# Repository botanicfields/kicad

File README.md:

# kicad
Projects

BF-002: Terminator for TLC5940

BF-005: 16-Segment LED controlled by TLC5940

BF-010: M5Stack interface for TLC5940 and HT16K33

BF-012: Arduino-Uno interface for TLC5940

libraries and footprints used by the projects above, or not used.

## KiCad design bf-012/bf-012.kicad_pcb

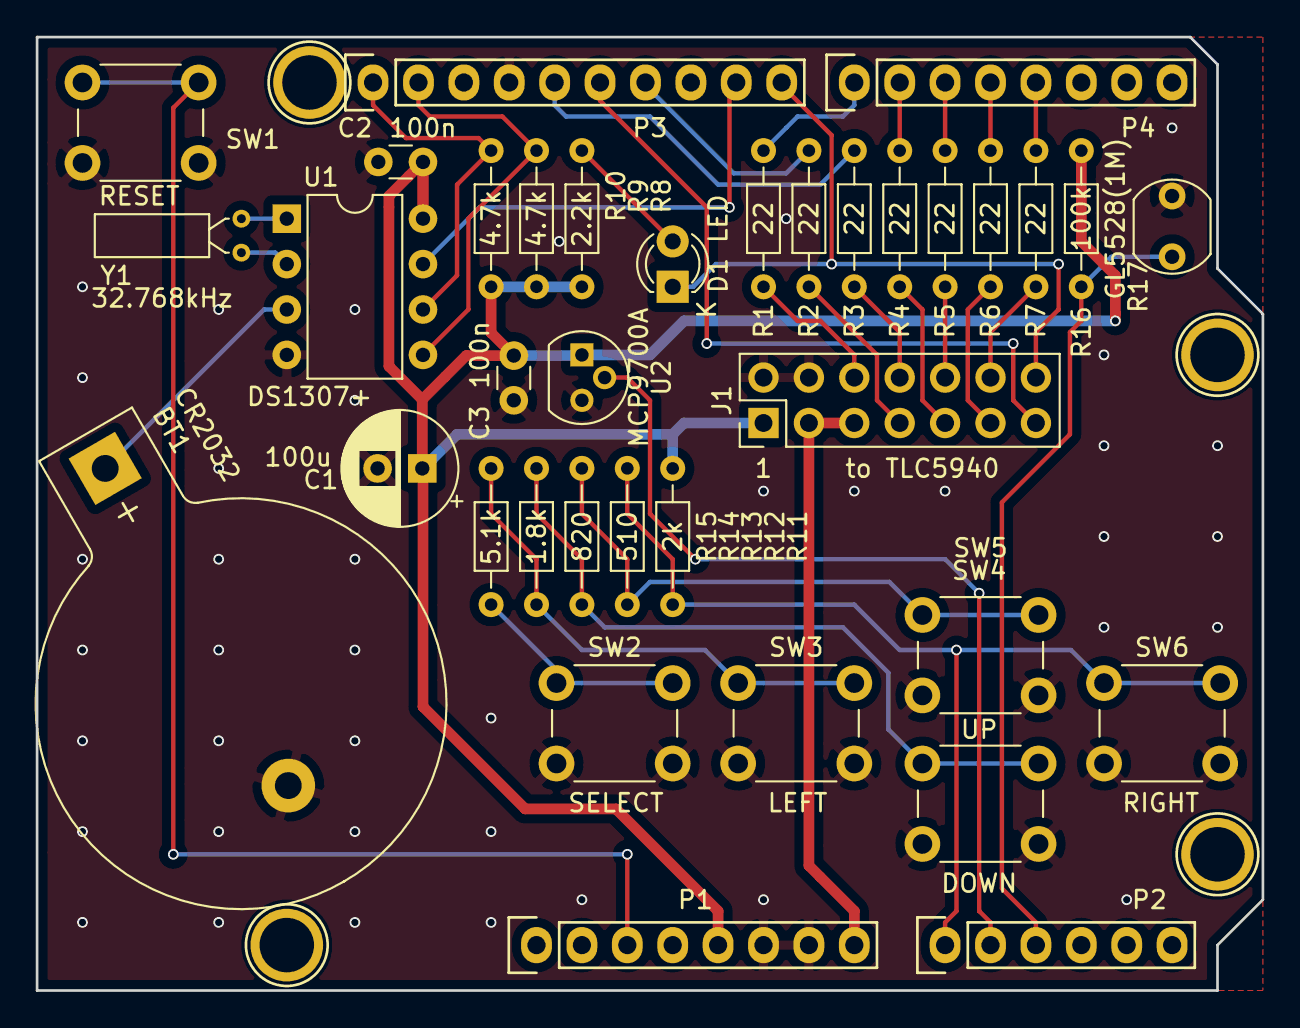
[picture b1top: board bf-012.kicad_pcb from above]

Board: 2 copper layers, 68.6 x 53.3 mm, 40 parts (0 on the bottom side), 34 nets.

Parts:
BT1: CR2032; BF@BatteryHolder_Keystone_103_1x20mm
C1: 100u; CP_Radial_D6.3mm_P2.50mm
C2, C3: 100n; C_Disc_D3.0mm_W1.6mm_P2.50mm
D1: LED; LED_D3.0mm
J1: Conn_02x07_Odd_Even; PinHeader_2x07_P2.54mm_Vertical
P1: Power; Socket_Strip_Arduino_1x08
P2: Analog; Socket_Strip_Arduino_1x06
P3: Digital; Socket_Strip_Arduino_1x10
P4: Digital; Socket_Strip_Arduino_1x08
P5, P6, P7, P8: CONN_01X01; Arduino_1pin
R1, R2, R3, R4, R5, R6, R7: 22; R_Axial_DIN0204_L3.6mm_D1.6mm_P7.62mm_Horizontal
R8: 2.2k; R_Axial_DIN0204_L3.6mm_D1.6mm_P7.62mm_Horizontal
R9, R10: 4.7k; R_Axial_DIN0204_L3.6mm_D1.6mm_P7.62mm_Horizontal
R11: 2k; R_Axial_DIN0204_L3.6mm_D1.6mm_P7.62mm_Horizontal
R12: 510; R_Axial_DIN0204_L3.6mm_D1.6mm_P7.62mm_Horizontal
R13: 820; R_Axial_DIN0204_L3.6mm_D1.6mm_P7.62mm_Horizontal
R14: 1.8k; R_Axial_DIN0204_L3.6mm_D1.6mm_P7.62mm_Horizontal
R15: 5.1k; R_Axial_DIN0204_L3.6mm_D1.6mm_P7.62mm_Horizontal
R16: 100k; R_Axial_DIN0204_L3.6mm_D1.6mm_P7.62mm_Horizontal
R17: GL5528(1M); R_LDR_5.1x4.3mm_P3.4mm_Vertical
SW1: RESET; SW_PUSH_6mm
SW2: SELECT; SW_PUSH_6mm
SW3: LEFT; SW_PUSH_6mm
SW4: DOWN; SW_PUSH_6mm
SW5: UP; SW_PUSH_6mm
SW6: RIGHT; SW_PUSH_6mm
U1: DS1307+; DIP-8_W7.62mm
U2: MCP9700A; TO-92
Y1: 32.768kHz; Crystal_DS26_D2.0mm_L6.0mm_Horizontal

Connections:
+5V: C1.1, C2.1, C3.1, J1.1, P1.5, R8.1, R9.1, R10.1, R11.1, R16.1, U1.8, U2.1
/3(**): P4.5, R7.1
/4: P4.4, R6.1
/5(**): P4.3, R5.1
/6(**): P4.2, R4.1
/7: P4.1, R1.1
/8: D1.1, J1.14, P3.10
/9(**): P3.9, U1.7
/11(**MOSI): P3.7, R2.1
/12(MISO): J1.13, P3.6
/13(SCK): P3.5, R3.1
/A0: P2.1, R11.2, R12.1, SW6.1
/A1: P2.2, U2.2
/A2: P2.3, R16.2, R17.1
/A4(SDA): P3.2, R9.2, U1.5
/A5(SCL): P3.1, R10.2, U1.6
/BLANK: J1.10, R5.2
/DCPRG: J1.11, R6.2
/GSCLK: J1.12, R7.2
/Reset: P1.3, SW1.1
/SCLK: J1.8, R3.2
/SIN: J1.7, R2.2
/VPRG: J1.6, R1.2
/Vin: J1.3, J1.5, P1.8
/XLAT: J1.9, R4.2
GND: BT1.2, C1.2, C2.2, C3.2, J1.2, J1.4, P1.6, P1.7, P3.4, R17.2, SW1.2, SW2.2, SW3.2, SW4.2, SW5.2, SW6.2, U1.4, U2.3
unnamed: BT1.1, U1.3
unnamed: D1.2, R8.2
unnamed: R12.2, R13.1, SW5.1
unnamed: R13.2, R14.1, SW4.1
unnamed: R14.2, R15.1, SW3.1
unnamed: R15.2, SW2.1
unnamed: U1.1, Y1.1
unnamed: U1.2, Y1.2

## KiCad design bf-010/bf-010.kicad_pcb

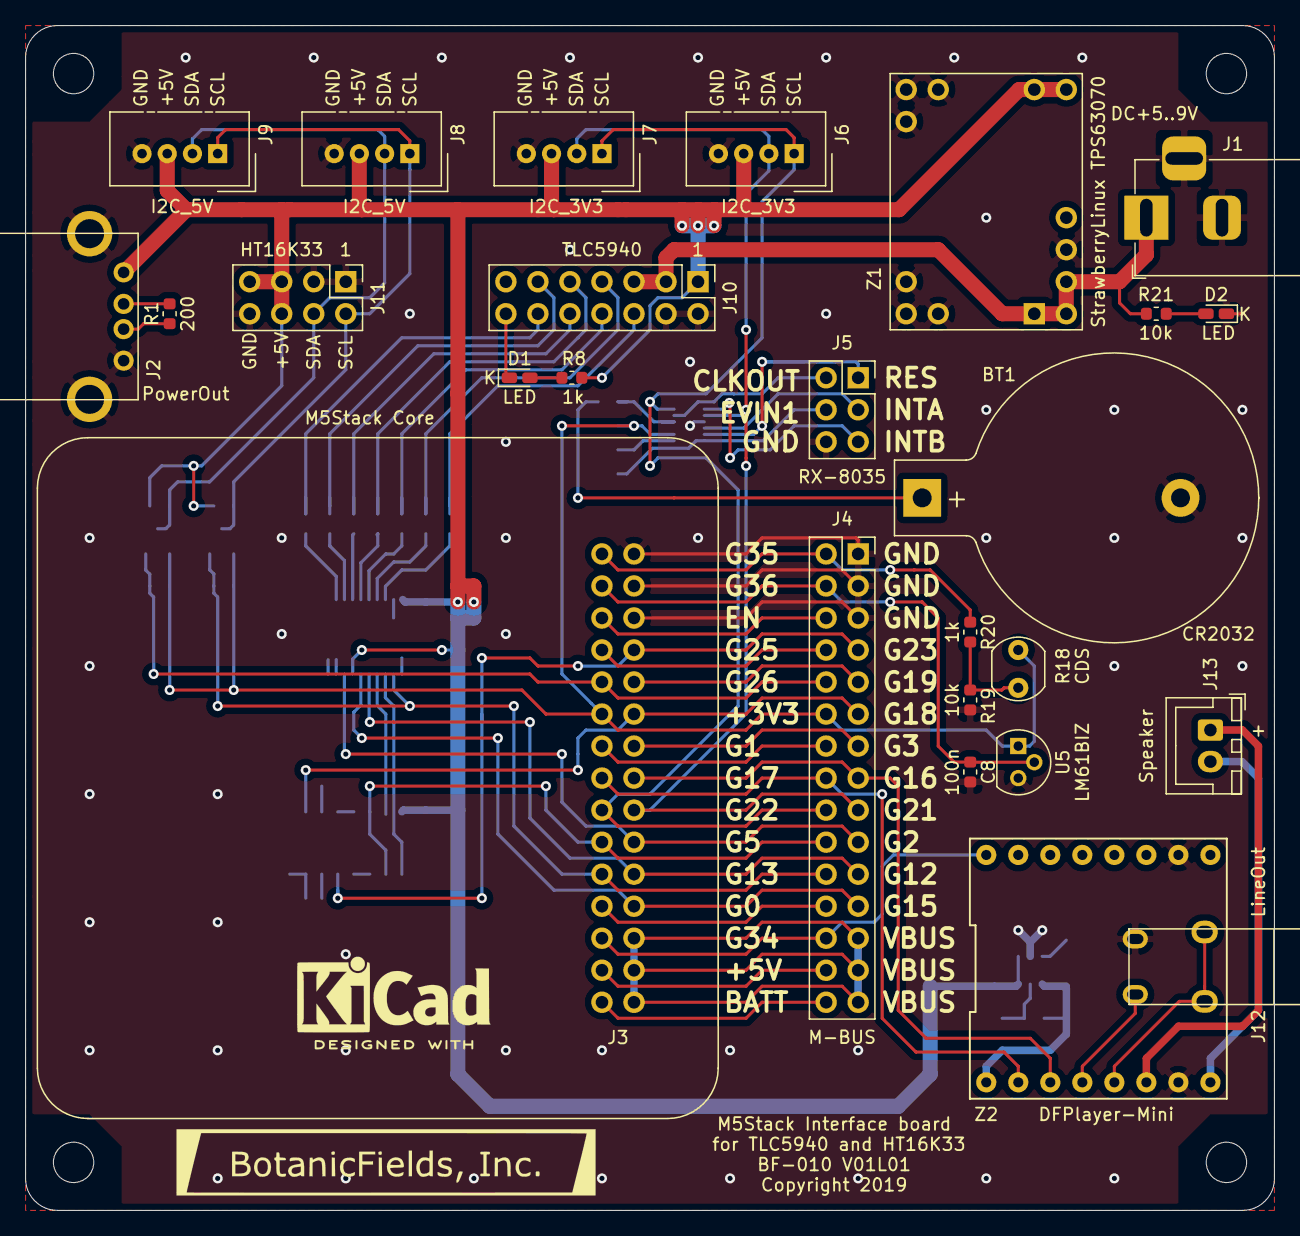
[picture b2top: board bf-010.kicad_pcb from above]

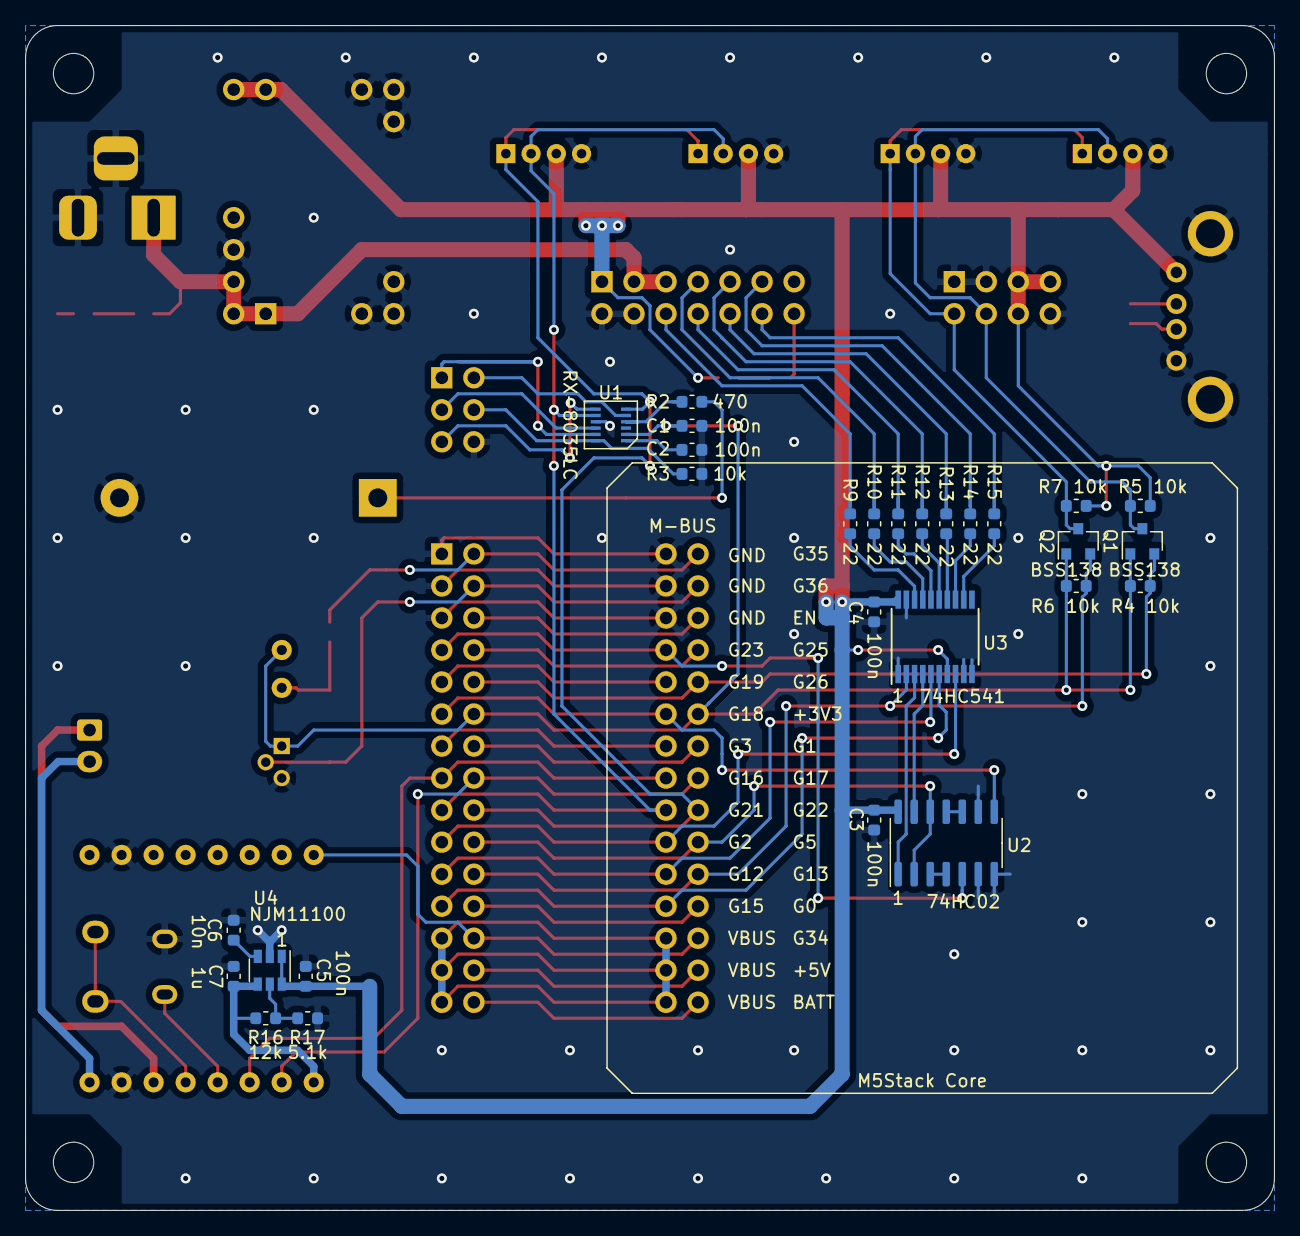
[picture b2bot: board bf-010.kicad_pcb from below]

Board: 2 copper layers, 99.1 x 94.0 mm, 54 parts (28 on the bottom side), 69 nets.

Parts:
BT1: CR2032; BF@BatteryHolder_Keystone_103_1x20mm
C1, C2, C3, C4, C5, C8: 100n; C_0603_1608Metric
C6: 10n; C_0603_1608Metric
C7: 1u; C_0603_1608Metric
D1, D2: LED; LED_0603_1608Metric_Castellated
J1: DC+5..9V; BarrelJack_Horizontal
J2: PowerOut; BF@USB-A-5075AR
J3: M-BUS; BF@M5Stack-Base
J4: M-BUS; PinSocket_2x15_P2.54mm_Vertical
J5: RX-8035; PinSocket_2x03_P2.54mm_Vertical
J6, J7: I2C_3V3; NS-Tech_Grove_1x04_P2mm_Vertical
J8, J9: I2C_5V; NS-Tech_Grove_1x04_P2mm_Vertical
J10: TLC5940; PinHeader_2x07_P2.54mm_Vertical
J11: HT16K33; PinHeader_2x04_P2.54mm_Vertical
J12: LineOut; BF@MJ8435
J13: Speaker; JST_XH_B2B-XH-A_1x02_P2.50mm_Vertical
Q1, Q2: BSS138; SOT-23
R1: 200; R_0603_1608Metric
R2: 470; R_0603_1608Metric
R3, R4, R5, R6, R7, R19, R21: 10k; R_0603_1608Metric
R8, R20: 1k; R_0603_1608Metric
R9, R10, R11, R12, R13, R14, R15: 22; R_0603_1608Metric
R16: 12k; R_0603_1608Metric
R17: 5.1k; R_0603_1608Metric
R18: CDS; R_LDR_5.0x4.1mm_P3mm_Vertical
U1: RX-8035LC; BF@VSOJ-12
U2: 74HC02; SOIC-14_3.9x8.7mm_P1.27mm
U3: 74HC541; TSSOP-20_4.4x6.5mm_P0.65mm
U4: NJM11100; SOT-23-6
U5: LM61BIZ; TO-92L
Z1: SbL-TPS63070; BF@SbL-TPS63070
Z2: DFPlayer-Mini; BF@MP3-TF-16P

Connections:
+3V3: C1.1, J3.12, J4.12, Q1.1, Q2.1, R4.1, R6.1, R18.1, U1.2, U5.1
+5V: J3.28, J4.28
+BATT: J3.30, J4.30
/BLANK: J10.10, R13.1
/DCPRG: J10.11, R14.1
/EN: J3.6, J4.6
/GPIO0: J3.24, J4.24
/GPIO1: J3.14, J4.14
/GPIO2: J3.19, J4.19, U3.8
/GPIO3: J3.13, J4.13
/GPIO5: J3.20, J4.20, U2.2, U2.12
/GPIO12: J3.21, J4.21, U3.5
/GPIO13: J3.22, J4.22, Q2.2, R6.2, U3.2
/GPIO15: J3.23, J4.23, U3.6
/GPIO16: J3.15, J4.15, Z2.3
/GPIO17: J3.16, J4.16, Z2.2
/GPIO18: J3.11, J4.11, U2.8
/GPIO19: J3.9, J4.9
/GPIO21: J3.17, J4.17, J6.2, J7.2, U1.8
/GPIO22: J3.18, J4.18, J6.1, J7.1, U1.6
/GPIO23: J3.7, J4.7, U2.5
/GPIO25: J3.8, J4.8
/GPIO26: J3.10, J4.10, Q1.2, R4.2
/GPIO34: J3.26, J4.26, Z2.16
/GPIO35: J3.2, J4.2, R20.1
/GPIO36: C8.1, J3.4, J4.4, U5.2
/GSCLK: J10.12, R15.1
/MOSI: J10.7, R10.1
/SCL5V: J8.1, J9.1, J11.2, Q2.3, R7.2
/SCLK: J10.8, R11.1
/SDA5V: J8.2, J9.2, J11.4, Q1.3, R5.2
/VPRG: J10.6, R9.1
/XERR: D1.1, J10.14
/XLAT: J10.9, R12.1
GND: BT1.2, C1.2, C2.2, C3.2, C4.2, C5.2, C6.2, C7.2, C8.2, D2.1, J1.2, J1.3, J2.4, J2.5, J3.1, J3.3, J3.5, J4.1, J4.3, J4.5, J5.6, J6.4, J7.4, J8.4, J9.4, J10.2, J10.4, J11.1, J11.3, J11.8, J12.S, R3.2, R17.2, R19.2, U1.9, U2.6, U2.7, U2.9, U3.1, U3.9, U3.10, U3.19, U4.2, U5.3, Z1.4, Z1.8, Z1.9, Z1.10, Z1.11, Z1.12, Z1.13, Z2.7, Z2.10
unnamed: BT1.1, R2.2
unnamed: C2.1, U1.1
unnamed: C6.1, U4.3
unnamed: C7.1, R16.1, U4.4, Z2.1
unnamed: D1.2, R8.2
unnamed: D2.2, R21.2
unnamed: J2.2, R1.2
unnamed: J2.3, R1.1
unnamed: J5.1, U1.11
unnamed: J5.2, U1.5
unnamed: J5.3, U1.10
unnamed: J5.4, R3.1, U1.12
unnamed: J5.5, U1.7
unnamed: J12.R, Z2.4
unnamed: J12.T, Z2.5
unnamed: J13.1, Z2.6
unnamed: J13.2, Z2.8
unnamed: R2.1, U1.4
unnamed: R9.2, U3.18
unnamed: R10.2, U3.17
unnamed: R11.2, U3.16
unnamed: R12.2, U3.15
unnamed: R13.2, U3.14
unnamed: R14.2, U3.13
unnamed: R15.2, U3.12
unnamed: R16.2, R17.1, U4.5
unnamed: R18.2, R19.1, R20.2
unnamed: U2.1, U3.3
unnamed: U2.3, U2.4
unnamed: U2.10, U2.11
unnamed: U2.13, U3.4
VBUS: J3.25, J3.27, J3.29, J4.25, J4.27, J4.29
VCC: C3.1, C4.1, C5.1, J2.1, J6.3, J7.3, J8.3, J9.3, J10.1, J11.5, J11.6, J11.7, R5.1, R7.1, R8.1, U2.14, U3.7, U3.20, U4.1, U4.6, Z1.6, Z1.7
VD: J1.1, J10.3, J10.5, R21.1, Z1.1, Z1.2, Z1.3

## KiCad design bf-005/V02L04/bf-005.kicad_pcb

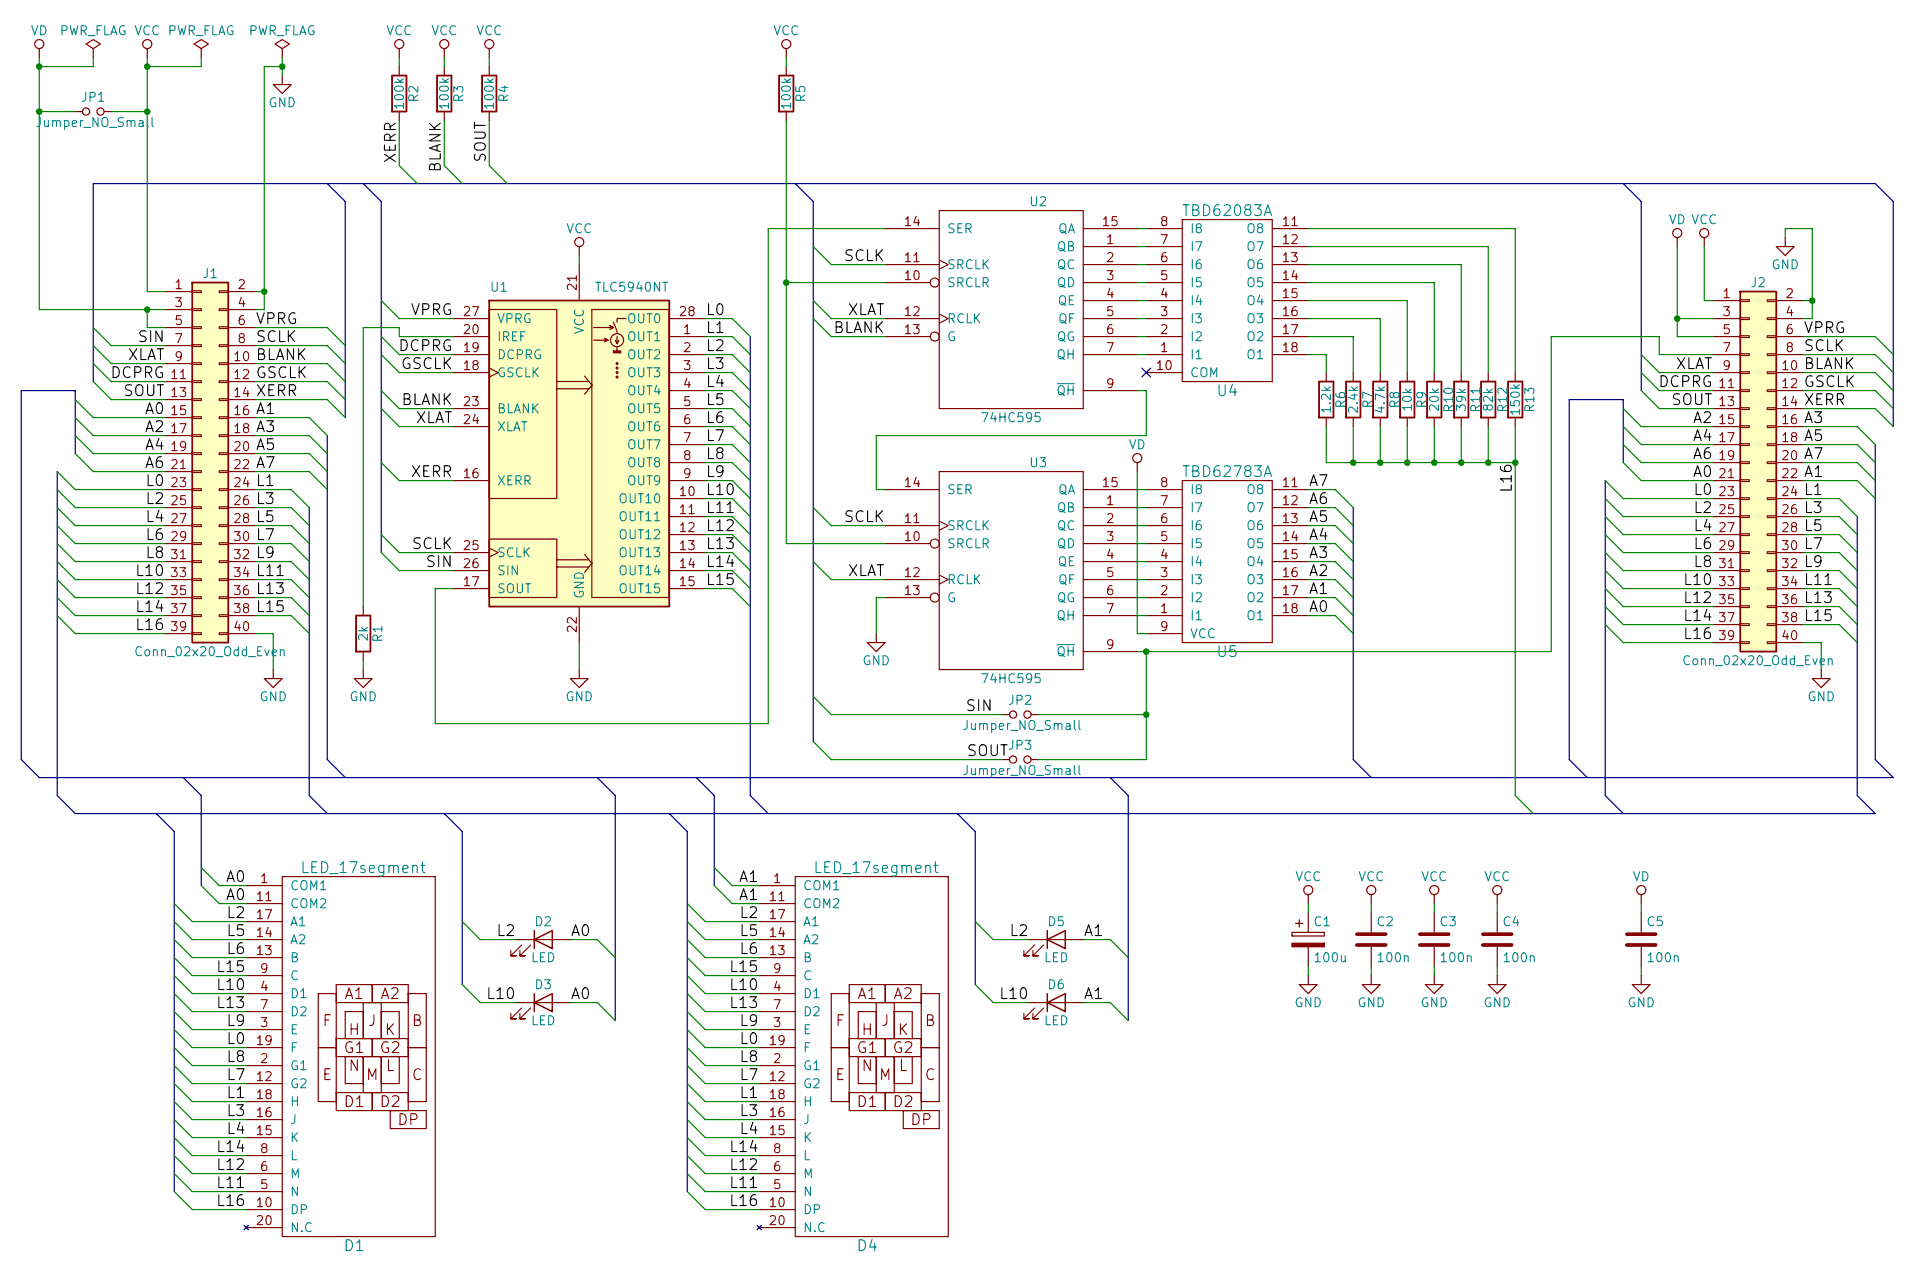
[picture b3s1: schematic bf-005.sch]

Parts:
C1: 100u; CP_Radial_D6.3mm_P2.50mm
C2, C3, C4, C5: 100n; C_Disc_D3.0mm_W1.6mm_P2.50mm
D1, D4: LED_17segment; BF@KA2311-42B
D2, D3, D5, D6: LED; LED_D5.0mm
J1: Conn_02x20_Odd_Even; PinHeader_2x20_P2.54mm_Horizontal
J2: Conn_02x20_Odd_Even; PinSocket_2x20_P2.54mm_Horizontal
JP1, JP2, JP3: Jumper_NO_Small; BF@jumper_pad_open
R1: 2k; R_Axial_DIN0204_L3.6mm_D1.6mm_P7.62mm_Horizontal
R2, R3, R4, R5: 100k; R_Axial_DIN0204_L3.6mm_D1.6mm_P7.62mm_Horizontal
R6: 1.2k; R_Axial_DIN0204_L3.6mm_D1.6mm_P7.62mm_Horizontal
R7: 2.4k; R_Axial_DIN0204_L3.6mm_D1.6mm_P7.62mm_Horizontal
R8: 4.7k; R_Axial_DIN0204_L3.6mm_D1.6mm_P7.62mm_Horizontal
R9: 10k; R_Axial_DIN0204_L3.6mm_D1.6mm_P7.62mm_Horizontal
R10: 20k; R_Axial_DIN0204_L3.6mm_D1.6mm_P7.62mm_Horizontal
R11: 39k; R_Axial_DIN0204_L3.6mm_D1.6mm_P7.62mm_Horizontal
R12: 82k; R_Axial_DIN0204_L3.6mm_D1.6mm_P7.62mm_Horizontal
R13: 150k; R_Axial_DIN0204_L3.6mm_D1.6mm_P7.62mm_Horizontal
U1: TLC5940NT; DIP-28_W7.62mm
U2, U3: 74HC595; DIP-16_W7.62mm
U4: TBD62083A; DIP-18_W7.62mm
U5: TBD62783A; DIP-18_W7.62mm

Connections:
/A0: D1.1 (COM1), D1.11 (COM2), D2.2 (A), D3.2 (A), J1.15, J2.21, U5.18 (O1)
/A1: D4.1 (COM1), D4.11 (COM2), D5.2 (A), D6.2 (A), J1.16, J2.22, U5.17 (O2)
/A2: J1.17, J2.15, U5.16 (O3)
/A3: J1.18, J2.16, U5.15 (O4)
/A4: J1.19, J2.17, U5.14 (O5)
/A5: J1.20, J2.18, U5.13 (O6)
/A6: J1.21, J2.19, U5.12 (O7)
/A7: J1.22, J2.20, U5.11 (O8)
/BLANK: J1.10, J2.10, R3.2, U1.23 (BLANK), U2.13 (G)
/DCPRG: J1.11, J2.11, U1.19 (DCPRG)
/GSCLK: J1.12, J2.12, U1.18 (GSCLK)
/L0: D1.19 (F), D4.19 (F), J1.23, J2.23, U1.28 (OUT0)
/L1: D1.18 (H), D4.18 (H), J1.24, J2.24, U1.1 (OUT1)
/L2: D1.17 (A1), D2.1 (K), D4.17 (A1), D5.1 (K), J1.25, J2.25, U1.2 (OUT2)
/L3: D1.16 (J), D4.16 (J), J1.26, J2.26, U1.3 (OUT3)
/L4: D1.15 (K), D4.15 (K), J1.27, J2.27, U1.4 (OUT4)
/L5: D1.14 (A2), D4.14 (A2), J1.28, J2.28, U1.5 (OUT5)
/L6: D1.13 (B), D4.13 (B), J1.29, J2.29, U1.6 (OUT6)
/L7: D1.12 (G2), D4.12 (G2), J1.30, J2.30, U1.7 (OUT7)
/L8: D1.2 (G1), D4.2 (G1), J1.31, J2.31, U1.8 (OUT8)
/L9: D1.3 (E), D4.3 (E), J1.32, J2.32, U1.9 (OUT9)
/L10: D1.4 (D1), D3.1 (K), D4.4 (D1), D6.1 (K), J1.33, J2.33, U1.10 (OUT10)
/L11: D1.5 (N), D4.5 (N), J1.34, J2.34, U1.11 (OUT11)
/L12: D1.6 (M), D4.6 (M), J1.35, J2.35, U1.12 (OUT12)
/L13: D1.7 (D2), D4.7 (D2), J1.36, J2.36, U1.13 (OUT13)
/L14: D1.8 (L), D4.8 (L), J1.37, J2.37, U1.14 (OUT14)
/L15: D1.9 (C), D4.9 (C), J1.38, J2.38, U1.15 (OUT15)
/L16: D1.10 (DP), D4.10 (DP), J1.39, J2.39, R6.2, R7.2, R8.2, R9.2, R10.2, R11.2, R12.2, R13.2
/SCLK: J1.8, J2.8, U1.25 (SCLK), U2.11 (SRCLK), U3.11 (SRCLK)
/SIN: J1.7, JP2.1, U1.26 (SIN)
/SOUT: J1.13, J2.13, JP3.1, R4.2
/VPRG: J1.6, J2.6, U1.27 (VPRG)
/XERR: J1.14, J2.14, R2.2, U1.16 (XERR)
/XLAT: J1.9, J2.9, U1.24 (XLAT), U2.12 (RCLK), U3.12 (RCLK)
GND: C1.2, C2.2, C3.2, C4.2, C5.2, J1.2, J1.4, J1.40, J2.2, J2.4, J2.40, R1.2, U1.22 (GND), U2.8 (GND), U3.8 (GND), U3.13 (G), U4.9 (GND), U5.10 (GND)
unnamed: J2.7, JP2.2, JP3.2, U3.9 (~QH)
unnamed: R1.1, U1.20 (IREF)
unnamed: R5.2, U2.10 (SRCLR), U3.10 (SRCLR)
unnamed: R6.1, U4.18 (O1)
unnamed: R7.1, U4.17 (O2)
unnamed: R8.1, U4.16 (O3)
unnamed: R9.1, U4.15 (O4)
unnamed: R10.1, U4.14 (O5)
unnamed: R11.1, U4.13 (O6)
unnamed: R12.1, U4.12 (O7)
unnamed: R13.1, U4.11 (O8)
unnamed: U1.17 (SOUT), U2.14 (SER)
unnamed: U2.1 (QB), U4.7 (I7)
unnamed: U2.2 (QC), U4.6 (I6)
unnamed: U2.3 (QD), U4.5 (I5)
unnamed: U2.4 (QE), U4.4 (I4)
unnamed: U2.5 (QF), U4.3 (I3)
unnamed: U2.6 (QG), U4.2 (I2)
unnamed: U2.7 (QH), U4.1 (I1)
unnamed: U2.9 (~QH), U3.14 (SER)
unnamed: U2.15 (QA), U4.8 (I8)
unnamed: U3.1 (QB), U5.7 (I7)
unnamed: U3.2 (QC), U5.6 (I6)
unnamed: U3.3 (QD), U5.5 (I5)
unnamed: U3.4 (QE), U5.4 (I4)
unnamed: U3.5 (QF), U5.3 (I3)
unnamed: U3.6 (QG), U5.2 (I2)
unnamed: U3.7 (QH), U5.1 (I1)
unnamed: U3.15 (QA), U5.8 (I8)
VCC: C1.1, C2.1, C3.1, C4.1, J1.1, J2.1, JP1.2, R2.1, R3.1, R4.1, R5.1, U1.21 (VCC), U2.16 (VCC), U3.16 (VCC)
VD: C5.1, J1.3, J1.5, J2.3, J2.5, JP1.1, U5.9 (VCC)

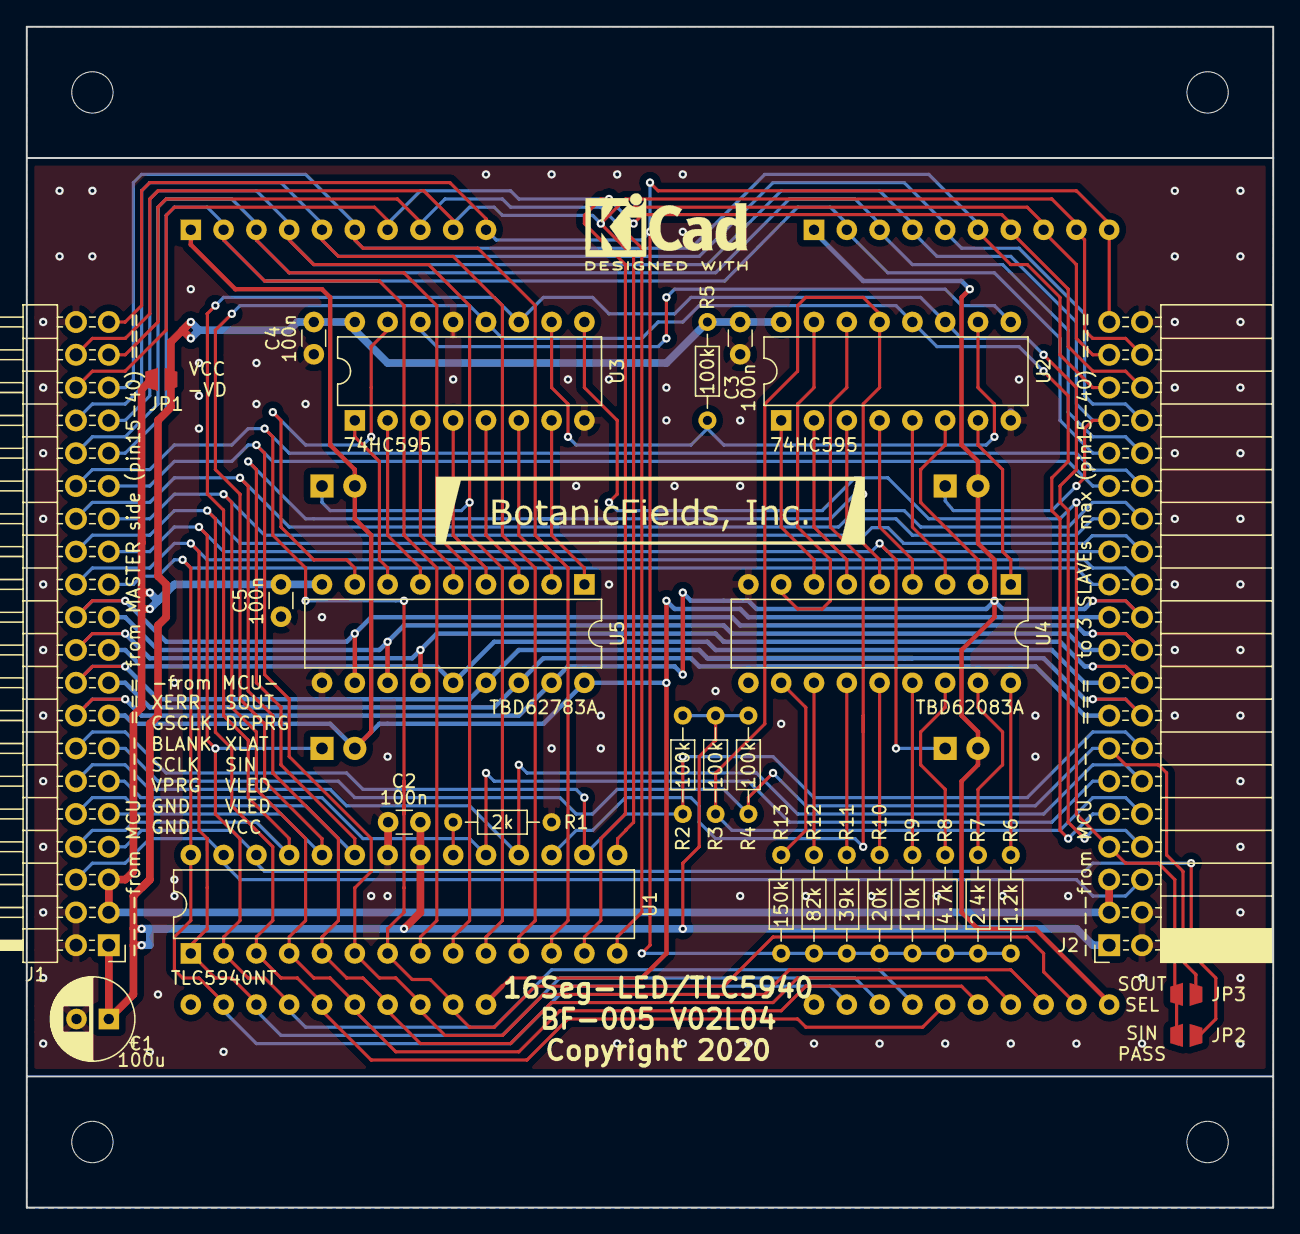
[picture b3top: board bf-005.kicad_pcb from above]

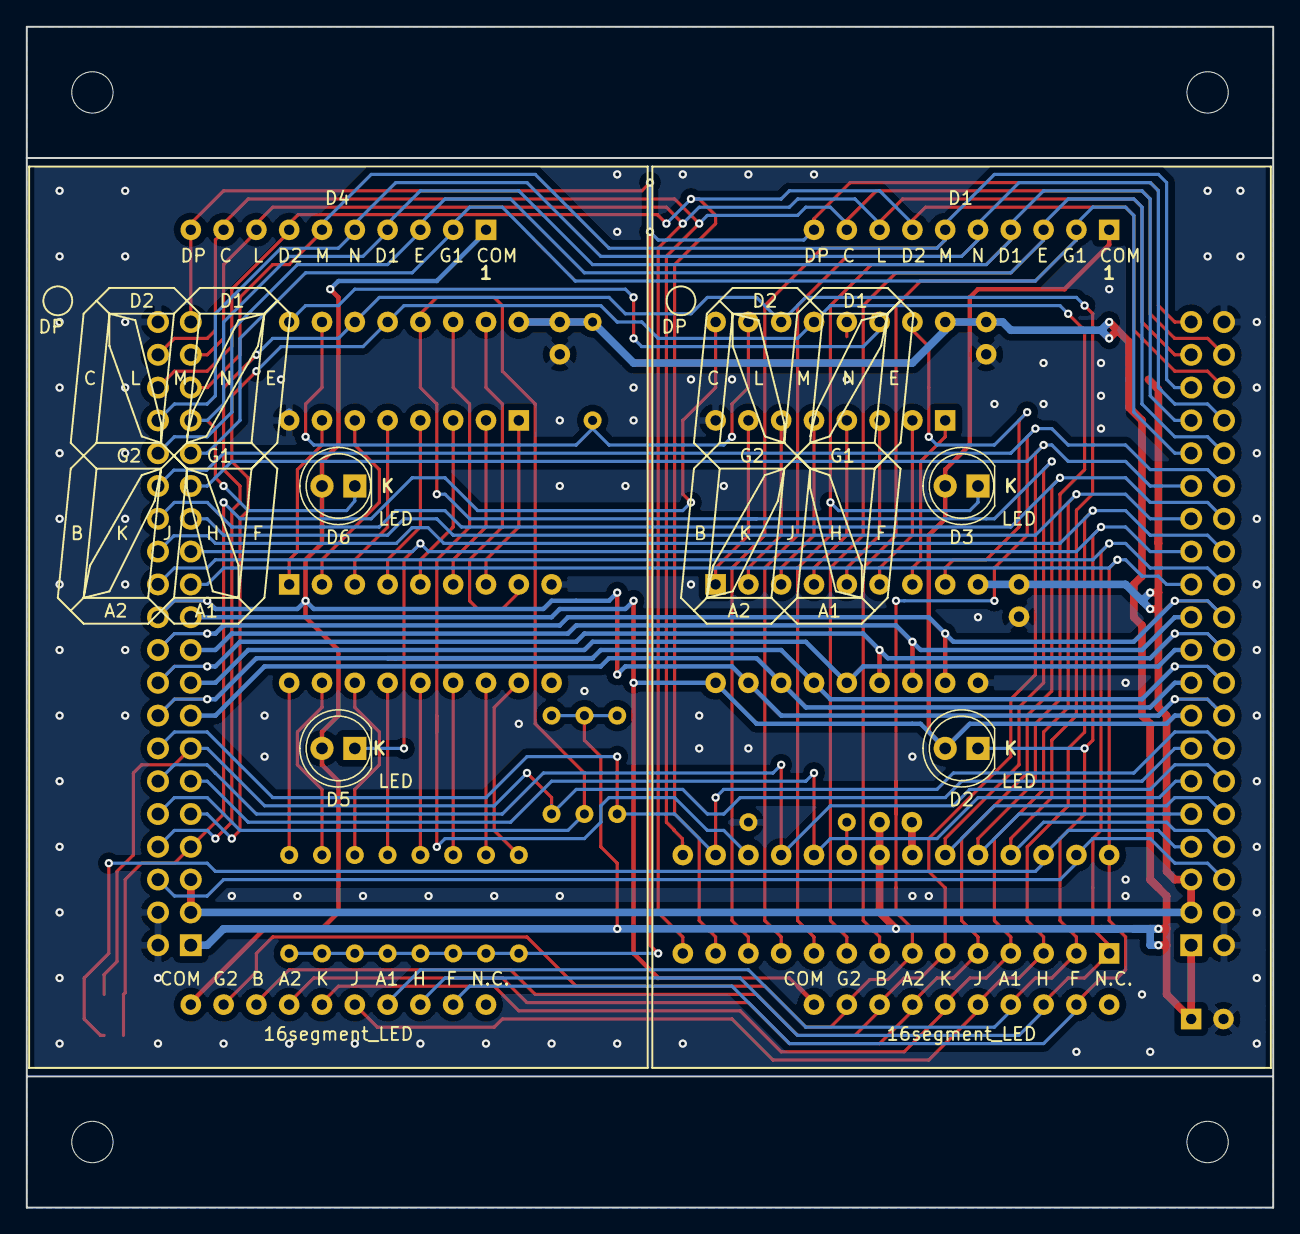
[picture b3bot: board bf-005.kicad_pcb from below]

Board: 2 copper layers, 96.5 x 91.4 mm, 34 parts (6 on the bottom side), 66 nets.

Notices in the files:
bf-005/V02L04/bf-005.kicad_pcb:
Copyright 2020 Botanic Fields, Inc.
bf-010/bf-010.kicad_pcb:
Copyright 2019 BotanicFields, Inc.
